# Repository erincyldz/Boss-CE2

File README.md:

Just me trying to learn PCB designing.
-
-
-
Plugins that i used:  
  -Freerouting - - - - - Can be downloaded directly at KiCAD-> Plugin Manager.
  -SchematicPositionsToLayout - - - - - - Can be downloaded from -> https://github.com/ian-ross/kicad-plugins

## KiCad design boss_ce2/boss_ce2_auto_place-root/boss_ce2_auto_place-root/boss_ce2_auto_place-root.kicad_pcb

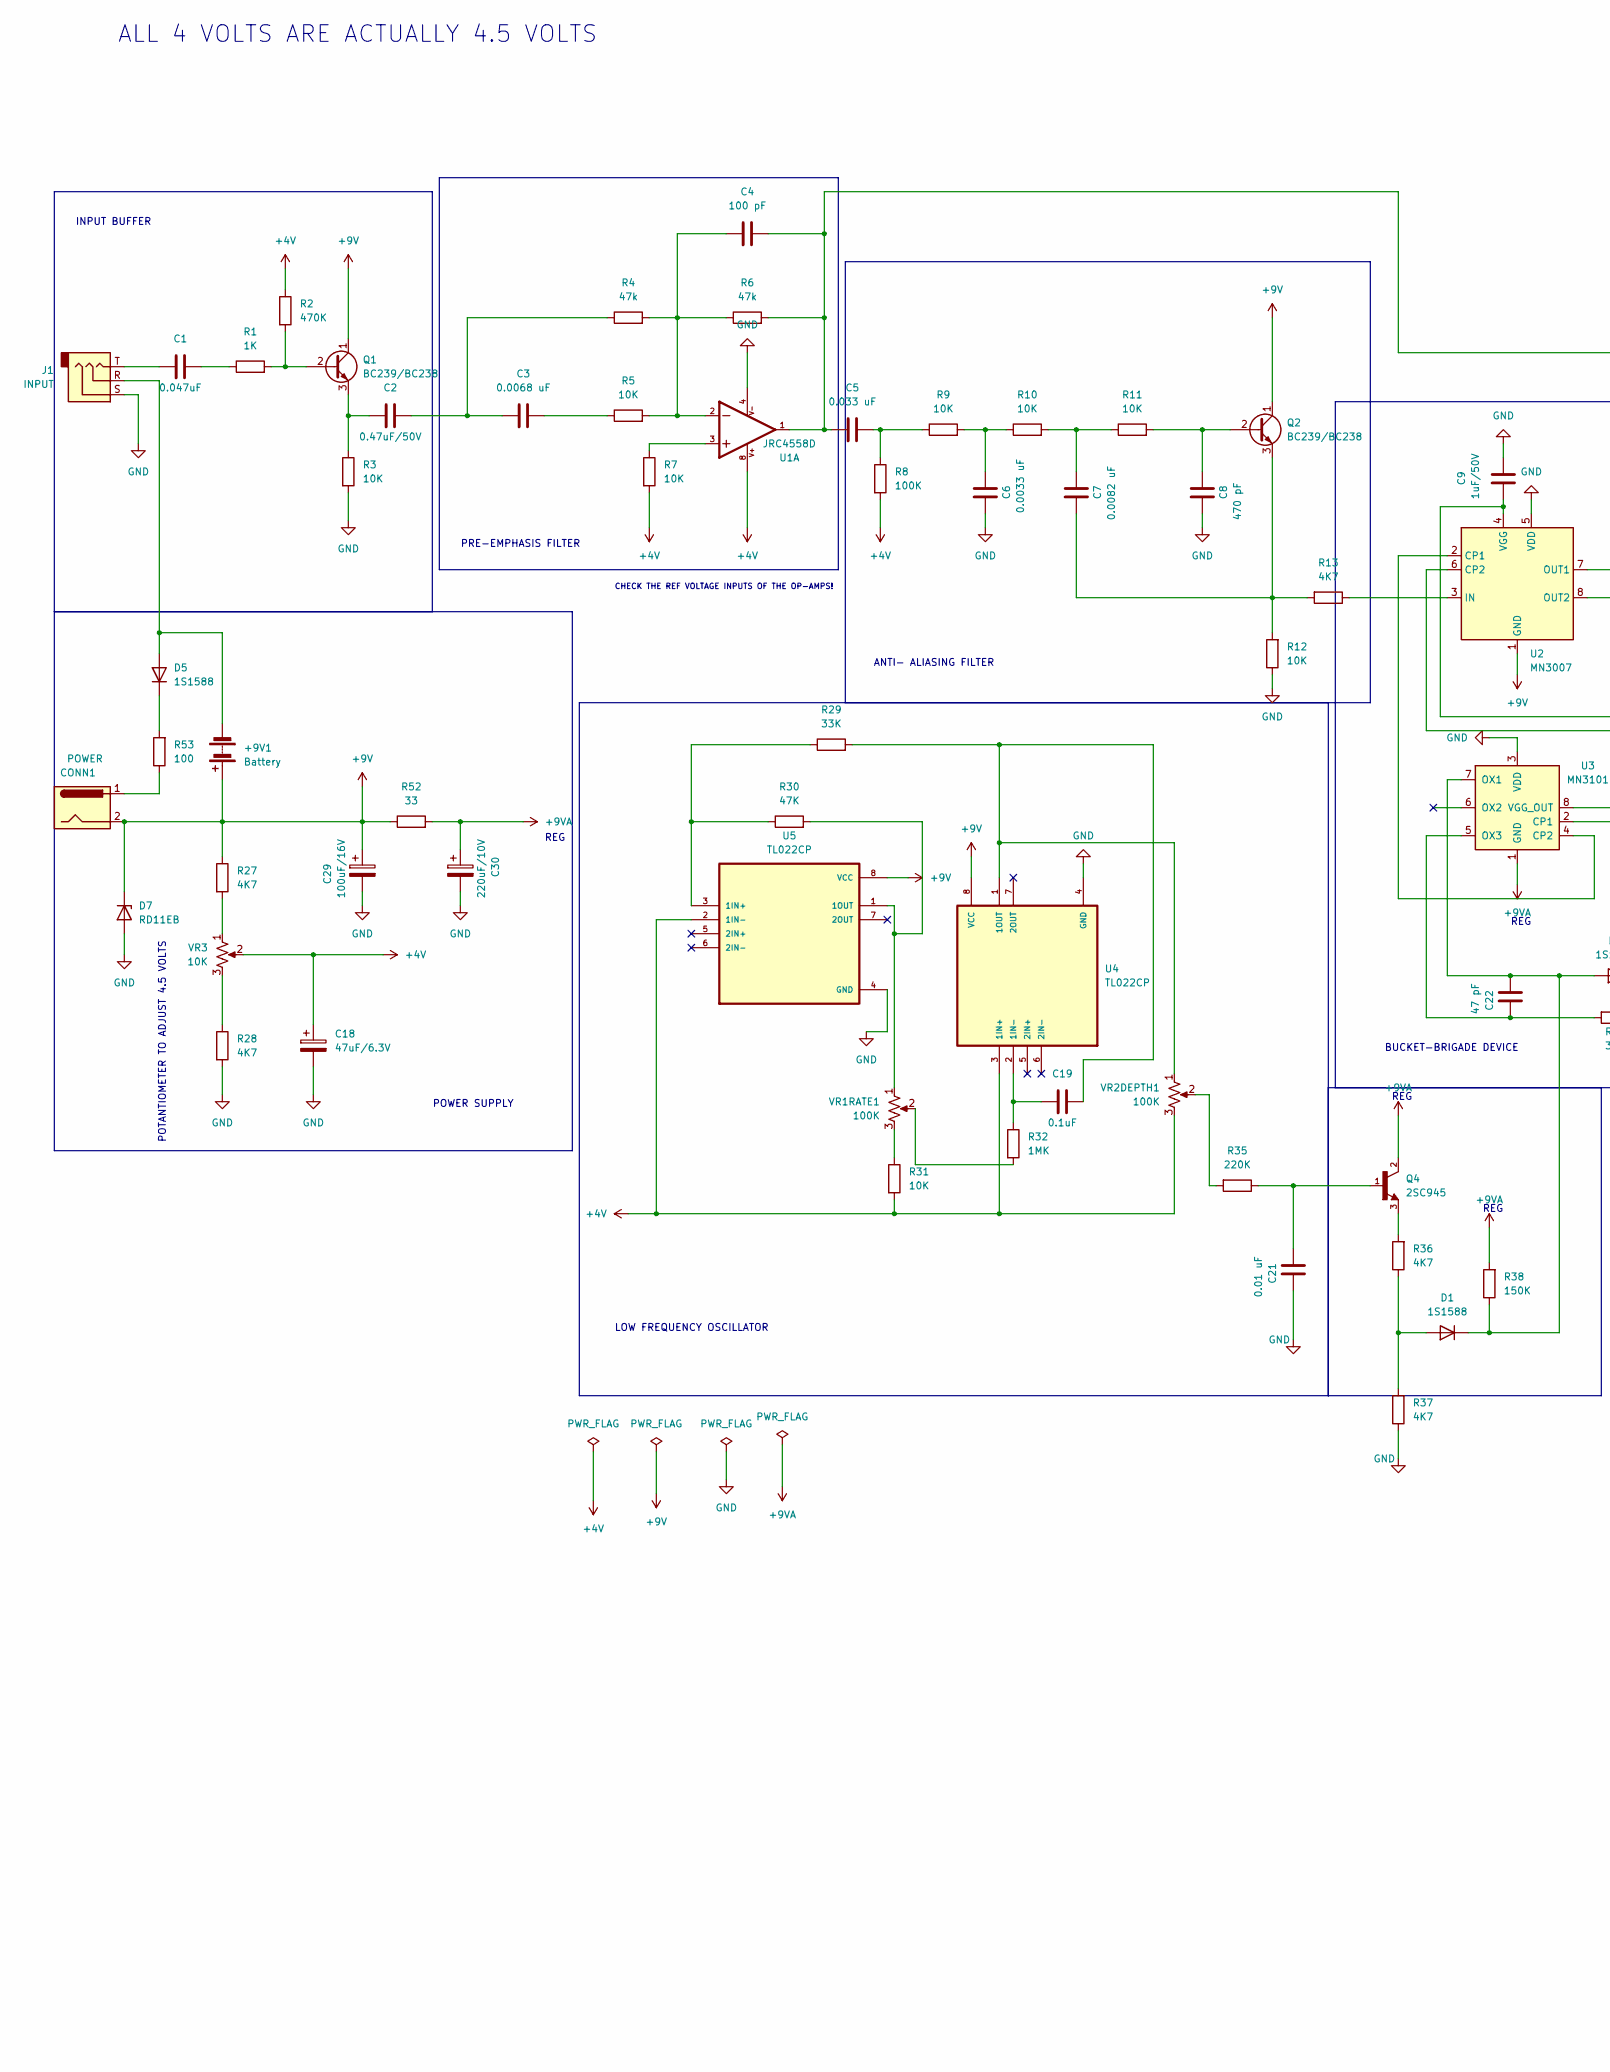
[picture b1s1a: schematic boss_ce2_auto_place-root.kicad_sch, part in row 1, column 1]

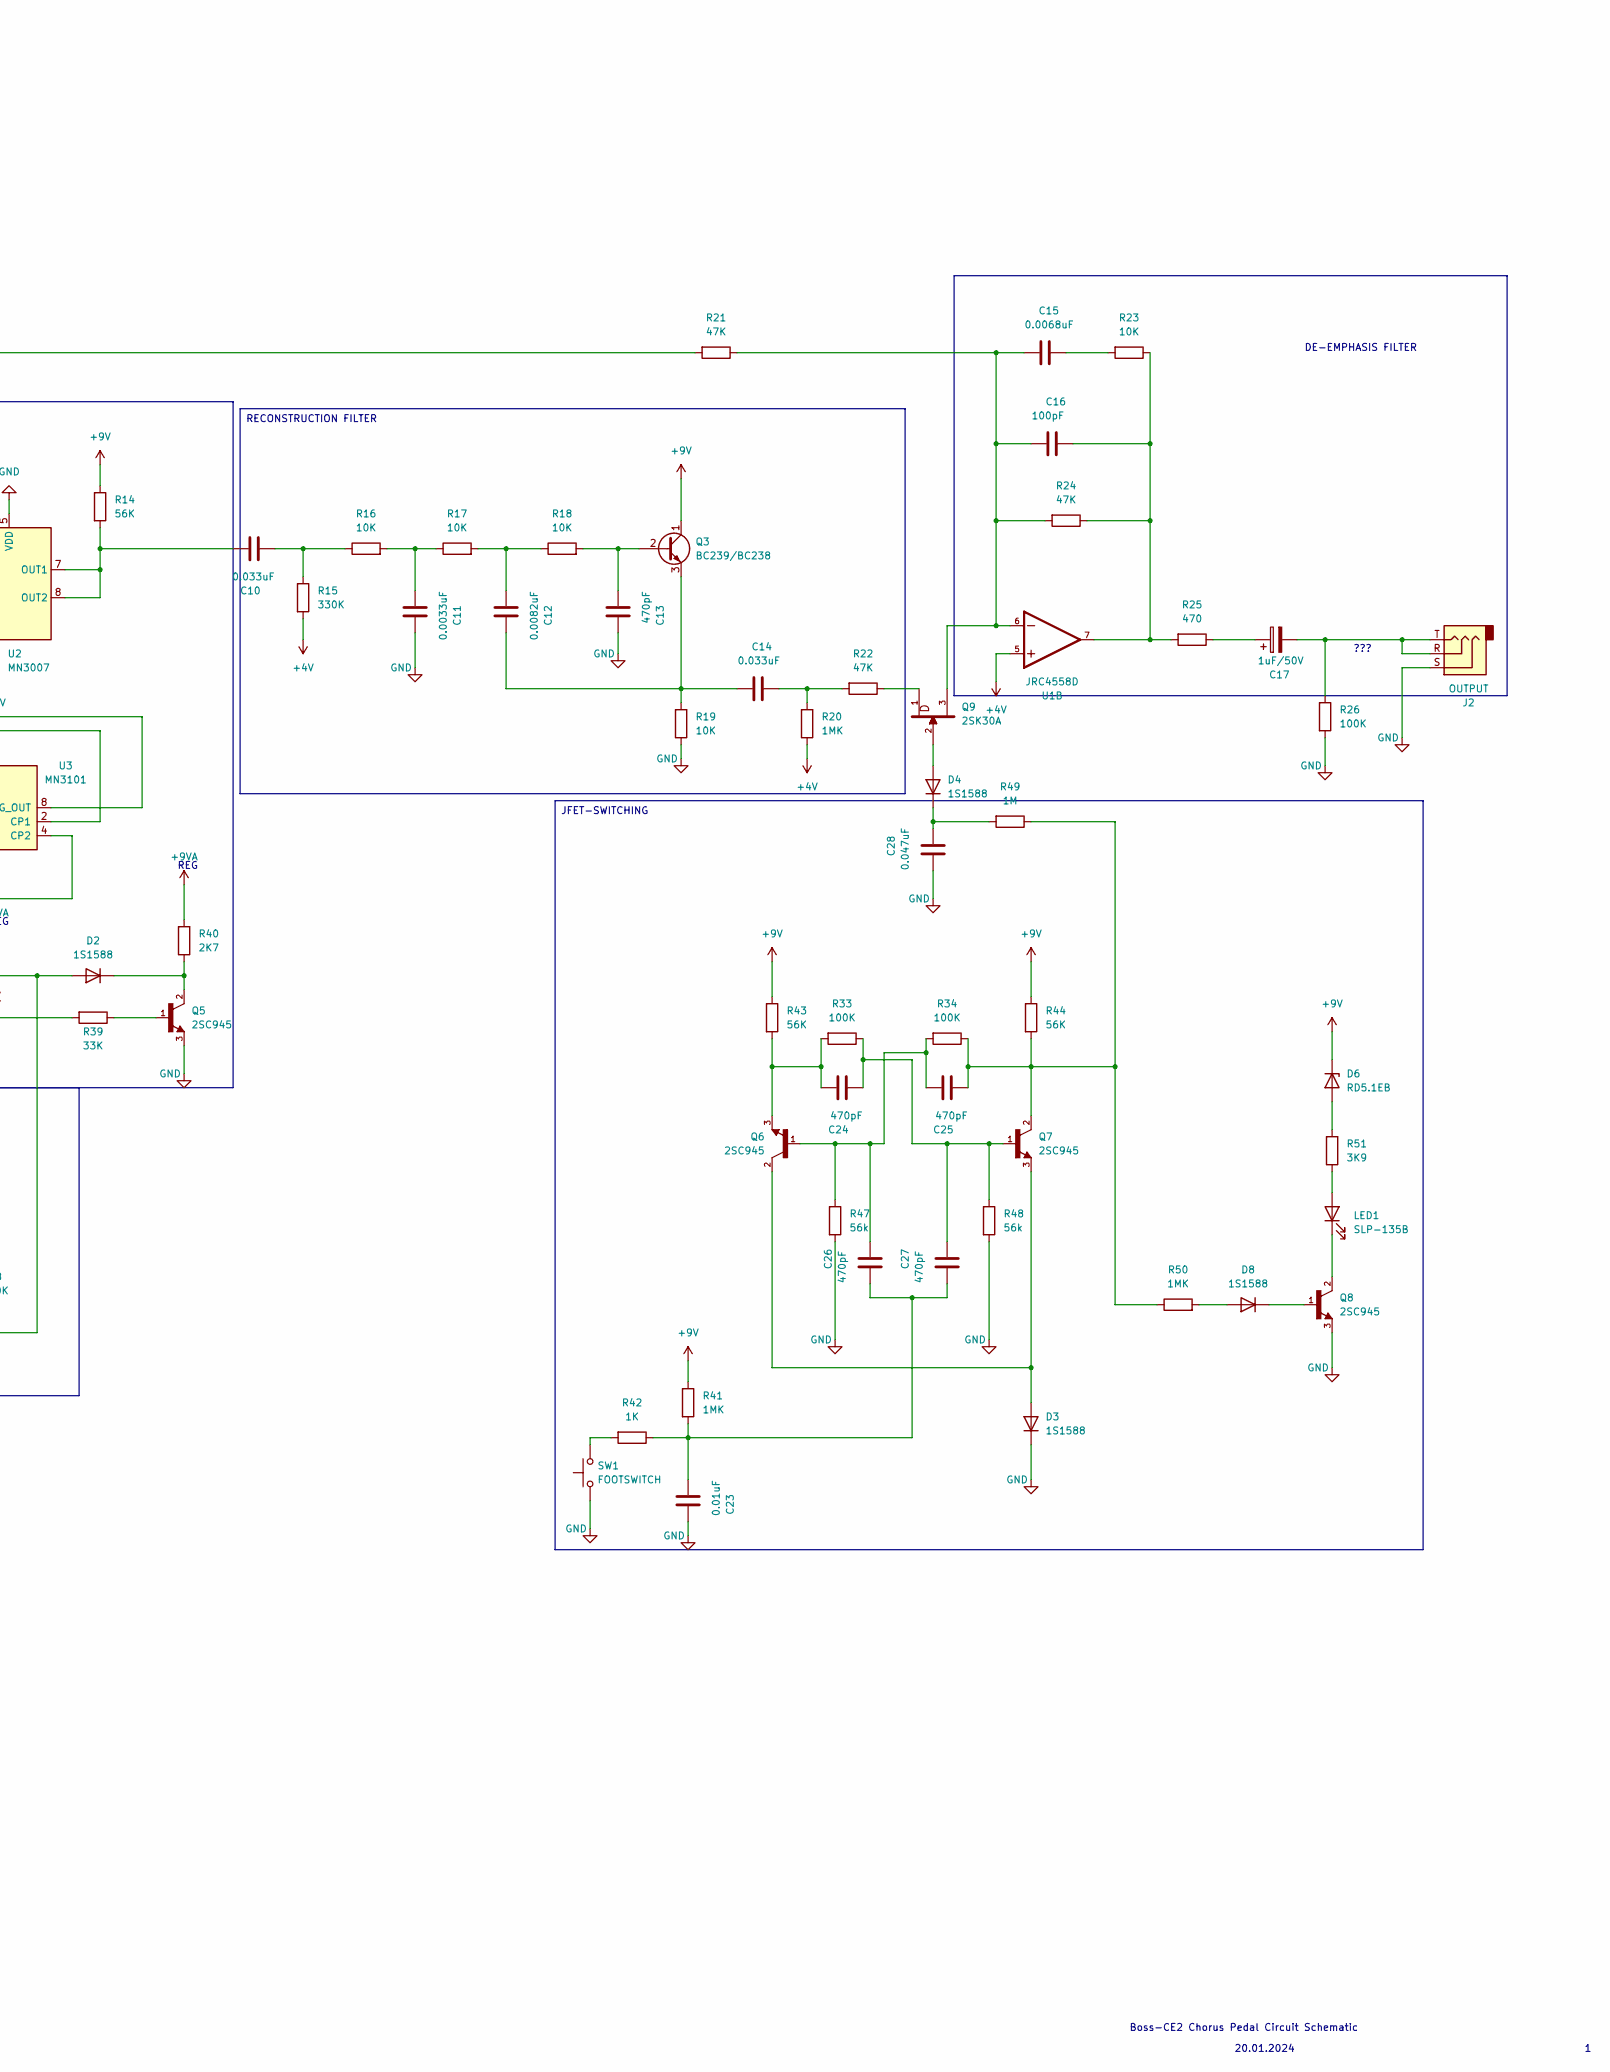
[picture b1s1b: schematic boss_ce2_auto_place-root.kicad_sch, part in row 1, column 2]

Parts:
+9V1: Battery; BatteryHolder_Keystone_2993
C1, C28: 0.047uF; C_0805_2012Metric
C2: 0.47uF/50V; C_0805_2012Metric
C3: 0.0068 uF; C_0805_2012Metric
C4: 100 pF; C_0805_2012Metric
C5: 0.033 uF; C_0805_2012Metric
C6: 0.0033 uF; C_0805_2012Metric
C7: 0.0082 uF; C_0805_2012Metric
C8: 470 pF; C_0805_2012Metric
C9: 1uF/50V; C_0805_2012Metric
C10, C14: 0.033uF; C_0805_2012Metric
C11: 0.0033uF; C_0805_2012Metric
C12: 0.0082uF; C_0805_2012Metric
C13, C24, C25, C26, C27: 470pF; C_0805_2012Metric
C15: 0.0068uF; C_0805_2012Metric
C16: 100pF; C_0805_2012Metric
C17: 1uF/50V; CP_Radial_D6.3mm_P2.50mm
C18: 47uF/6.3V; CP_Radial_D6.3mm_P2.50mm
C19: 0.1uF; C_0805_2012Metric
C21: 0.01 uF; C_0805_2012Metric
C22: 47 pF; C_0805_2012Metric
C23: 0.01uF; C_0805_2012Metric
C29: 100uF/16V; CP_Radial_D8.0mm_P3.50mm
C30: 220uF/10V; CP_Radial_D10.0mm_P5.00mm
CONN1: POWER; JWT_A3963_1x02_P3.96mm_Vertical
D1, D2, D3, D4, D5, D8: 1S1588; D_DO-35_SOD27_P3.81mm_Vertical_KathodeUp
D6: RD5.1EB; D_DO-15_P3.81mm_Vertical_KathodeUp
D7: RD11EB; D_DO-15_P3.81mm_Vertical_AnodeUp
J1: INPUT; Jack_6.35mm_Neutrik_NJ3FD-V_Vertical
J2: OUTPUT; Jack_6.35mm_Neutrik_NJ3FD-V_Vertical
LED1: SLP-135B; LED_D3.0mm
Q1, Q2, Q3: BC239/BC238; TO-92_Inline
Q4, Q5, Q6, Q7, Q8: 2SC945; TO92
Q9: 2SK30A; TO92
R1, R42: 1K; R_0805_2012Metric
R2: 470K; R_0805_2012Metric
R3, R5, R7, R9, R10, R11, R12, R16, R17, R18, R19, R23, R31: 10K; R_0805_2012Metric
R4, R6: 47k; R_0805_2012Metric
R8, R26, R33, R34: 100K; R_0805_2012Metric
R13, R27, R28, R36, R37: 4K7; R_0805_2012Metric
R14, R43, R44: 56K; R_0805_2012Metric
R15: 330K; R_0805_2012Metric
R20, R32, R41, R50: 1MK; R_0805_2012Metric
R21, R22, R24, R30: 47K; R_0805_2012Metric
R25: 470; R_0805_2012Metric
R29, R39: 33K; R_0805_2012Metric
R35: 220K; R_0805_2012Metric
R38: 150K; R_0805_2012Metric
R40: 2K7; R_0805_2012Metric
R47, R48: 56k; R_0805_2012Metric
R49: 1M; R_0805_2012Metric
R51: 3K9; R_0805_2012Metric
R52: 33; R_0805_2012Metric
R53: 100; R_0805_2012Metric
SW1: FOOTSWITCH; SW_PUSH_6mm_H5mm
U1: JRC4558D; DIP-8_W10.16mm
U2: MN3007; DIP-8_W7.62mm
U3: MN3101; DIP-8_W7.62mm
U4, U5: TL022CP; DIP794W45P254L959H508Q8
VR1RATE1, VR2DEPTH1: 100K; Potentiometer_ACP_CA6-H2,5_Horizontal
VR3: 10K; Potentiometer_ACP_CA6-H2,5_Horizontal

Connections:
+4V: C18.1, R2.1, R7.2, R8.2, R15.2, R20.1, R31.2, U1.5, U1.8, U4.3 (1IN+), U5.2 (1IN-), VR2DEPTH1.3, VR3.2
+9V: +9V1.1 (+), C29.1, CONN1.2, D6.1 (K), D7.1 (K), Q1.1 (C), Q2.1 (C), Q3.1 (C), R14.1, R27.1, R41.1, R43.1, R44.1, R52.1, U2.1 (GND), U4.8 (VCC), U5.8 (VCC)
+9VA: C30.1, Q4.2, R38.2, R40.2, R52.2, U3.1 (GND)
GND: C6.1, C8.1, C9.2, C11.2, C13.2, C18.2, C21.2, C23.2, C28.1, C29.2, C30.2, D3.1 (K), D7.2 (A), J1.S, J2.S, Q5.3, Q8.3, R3.2, R12.1, R19.1, R26.2, R28.2, R37.1, R47.2, R48.2, SW1.1, U1.4, U2.5 (VDD), U3.3 (VDD), U4.4 (GND), U5.4 (GND)
unnamed: +9V1.2 (-), D5.2 (A), J1.R
unnamed: C1.1, J1.T
unnamed: C1.2, R1.1
unnamed: C2.2, C3.1, R4.1
unnamed: C3.2, R5.1
unnamed: C4.1, R4.2, R5.2, R6.1, U1.2
unnamed: C4.2, C5.1, R6.2, R21.2, U1.1
unnamed: C5.2, R8.1, R9.1
unnamed: C6.2, R9.2, R10.1
unnamed: C7.2, R10.2, R11.1
unnamed: C10.1, R15.1, R16.1
unnamed: C11.1, R16.2, R17.1
unnamed: C12.1, R17.2, R18.1
unnamed: C14.2, R20.2, R22.2
unnamed: C15.1, C16.1, Q9.3, R21.1, R24.2, U1.6
unnamed: C15.2, R23.2
unnamed: C16.2, R23.1, R24.1, R25.2, U1.7
unnamed: C17.1, R25.1
unnamed: C17.2, J2.R, J2.T, R26.1
unnamed: C21.1, Q4.1, R35.1
unnamed: C23.1, C26.1, C27.1, R41.2, R42.1
unnamed: C24.1, C27.2, Q7.1, R33.1, R48.1
unnamed: C24.2, Q6.3, R33.2, R43.2
unnamed: C25.1, Q7.2, R34.1, R44.2, R49.1, R50.1
unnamed: C25.2, C26.2, Q6.1, R34.2, R47.1
unnamed: CONN1.1, R53.1
unnamed: D1.2 (A), R36.1, R37.2
unnamed: C22.1, D1.1 (K), D2.2 (A), R38.1, U3.7 (OX1)
unnamed: D2.1 (K), Q5.2, R40.1
unnamed: D3.2 (A), Q6.2, Q7.3
unnamed: D4.2 (A), Q9.2
unnamed: C28.2, D4.1 (K), R49.2
unnamed: D5.1 (K), R53.2
unnamed: D6.2 (A), R51.2
unnamed: D8.2 (A), R50.2
unnamed: D8.1 (K), Q8.1
unnamed: LED1.2 (A), R51.1
unnamed: LED1.1 (K), Q8.2
unnamed: Q1.2 (B), R1.2, R2.2
unnamed: C2.1, Q1.3 (E), R3.1
unnamed: C8.2, Q2.2 (B), R11.2
unnamed: C7.1, Q2.3 (E), R12.2, R13.2
unnamed: C13.1, Q3.2 (B), R18.2
unnamed: C12.2, C14.1, Q3.3 (E), R19.2
unnamed: Q4.3, R36.2
unnamed: Q5.1, R39.1
unnamed: Q9.1, R22.1
unnamed: R7.1, U1.3
unnamed: R27.2, VR3.1
unnamed: R28.1, VR3.3
unnamed: R31.1, VR1RATE1.3
unnamed: R32.2, VR1RATE1.2
unnamed: R35.2, VR2DEPTH1.2
unnamed: R42.2, SW1.2
unnamed: U2.2 (CP1), U3.4 (CP2)
unnamed: U2.6 (CP2), U3.2 (CP1)
unnamed: R13.1, U2.3 (IN)
unnamed: C10.2, R14.2, U2.7 (OUT1), U2.8 (OUT2)
unnamed: C9.1, U2.4 (VGG), U3.8 (VGG_OUT)
unnamed: C22.2, R39.2, U3.5 (OX3)
unnamed: C19.1, R32.1, U4.2 (1IN-)
unnamed: C19.2, R29.2, U4.1 (1OUT), VR2DEPTH1.1
unnamed: R29.1, R30.1, U5.3 (1IN+)
unnamed: R30.2, U5.1 (1OUT), VR1RATE1.1

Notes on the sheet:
JFET-SWITCHING
RECONSTRUCTION FILTER
REG
POTANTIOMETER TO ADJUST 4.5 VOLTS
ANTI- ALIASING FILTER
ALL 4 VOLTS ARE ACTUALLY 4.5 VOLTS
DE-EMPHASIS FILTER
BUCKET-BRIGADE DEVICE
PRE-EMPHASIS FILTER
Boss-CE2 Chorus Pedal Circuit Schematic
INPUT BUFFER
???
20.01.2024
POWER SUPPLY
LOW FREQUENCY OSCILLATOR
CHECK THE REF VOLTAGE INPUTS OF THE OP-AMPS!

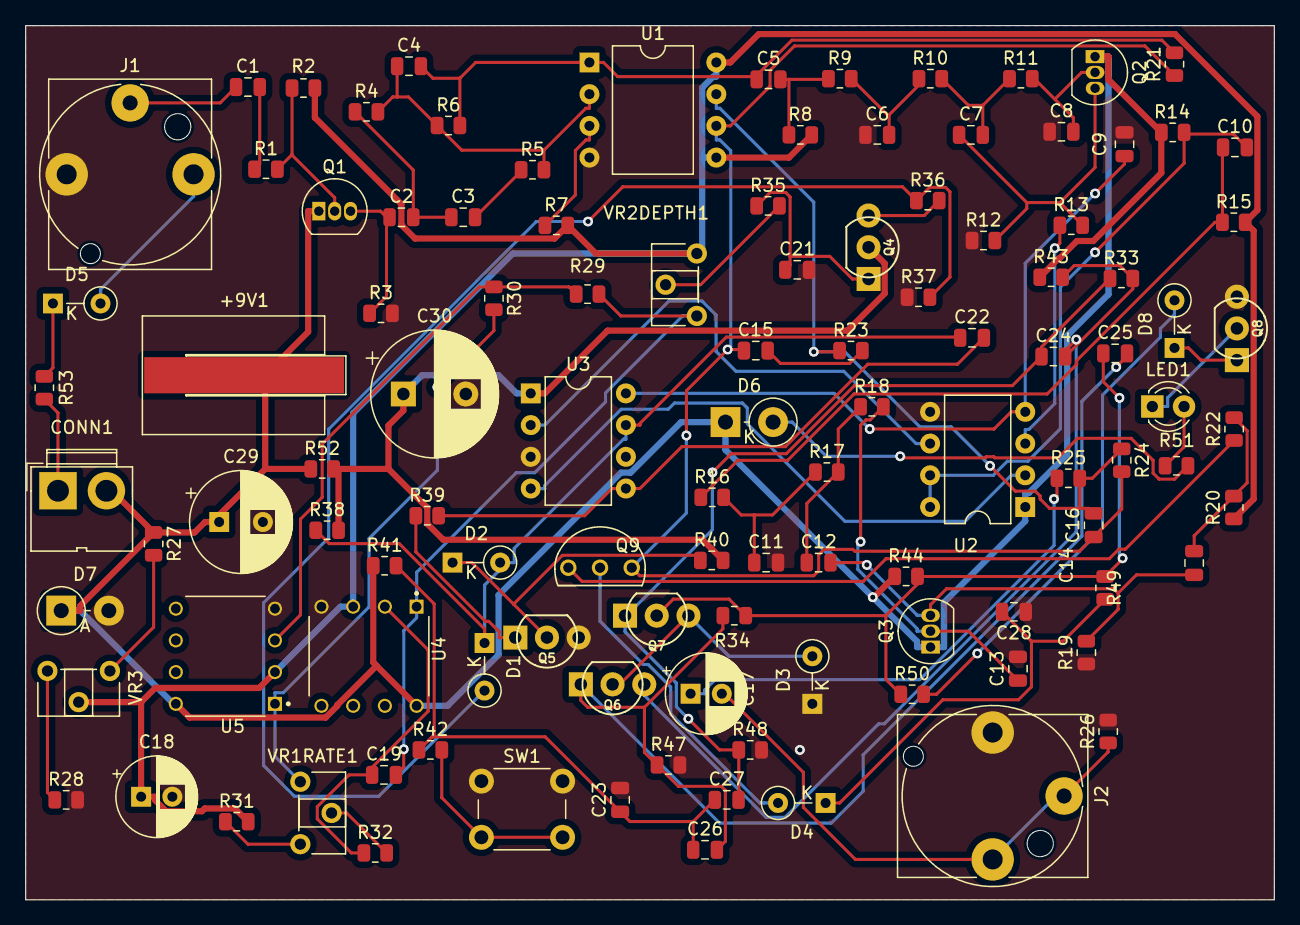
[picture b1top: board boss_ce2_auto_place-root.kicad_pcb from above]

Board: 2 copper layers, 100.0 x 70.0 mm, 111 parts (0 on the bottom side), 68 nets.

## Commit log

2024-01-26 push test
